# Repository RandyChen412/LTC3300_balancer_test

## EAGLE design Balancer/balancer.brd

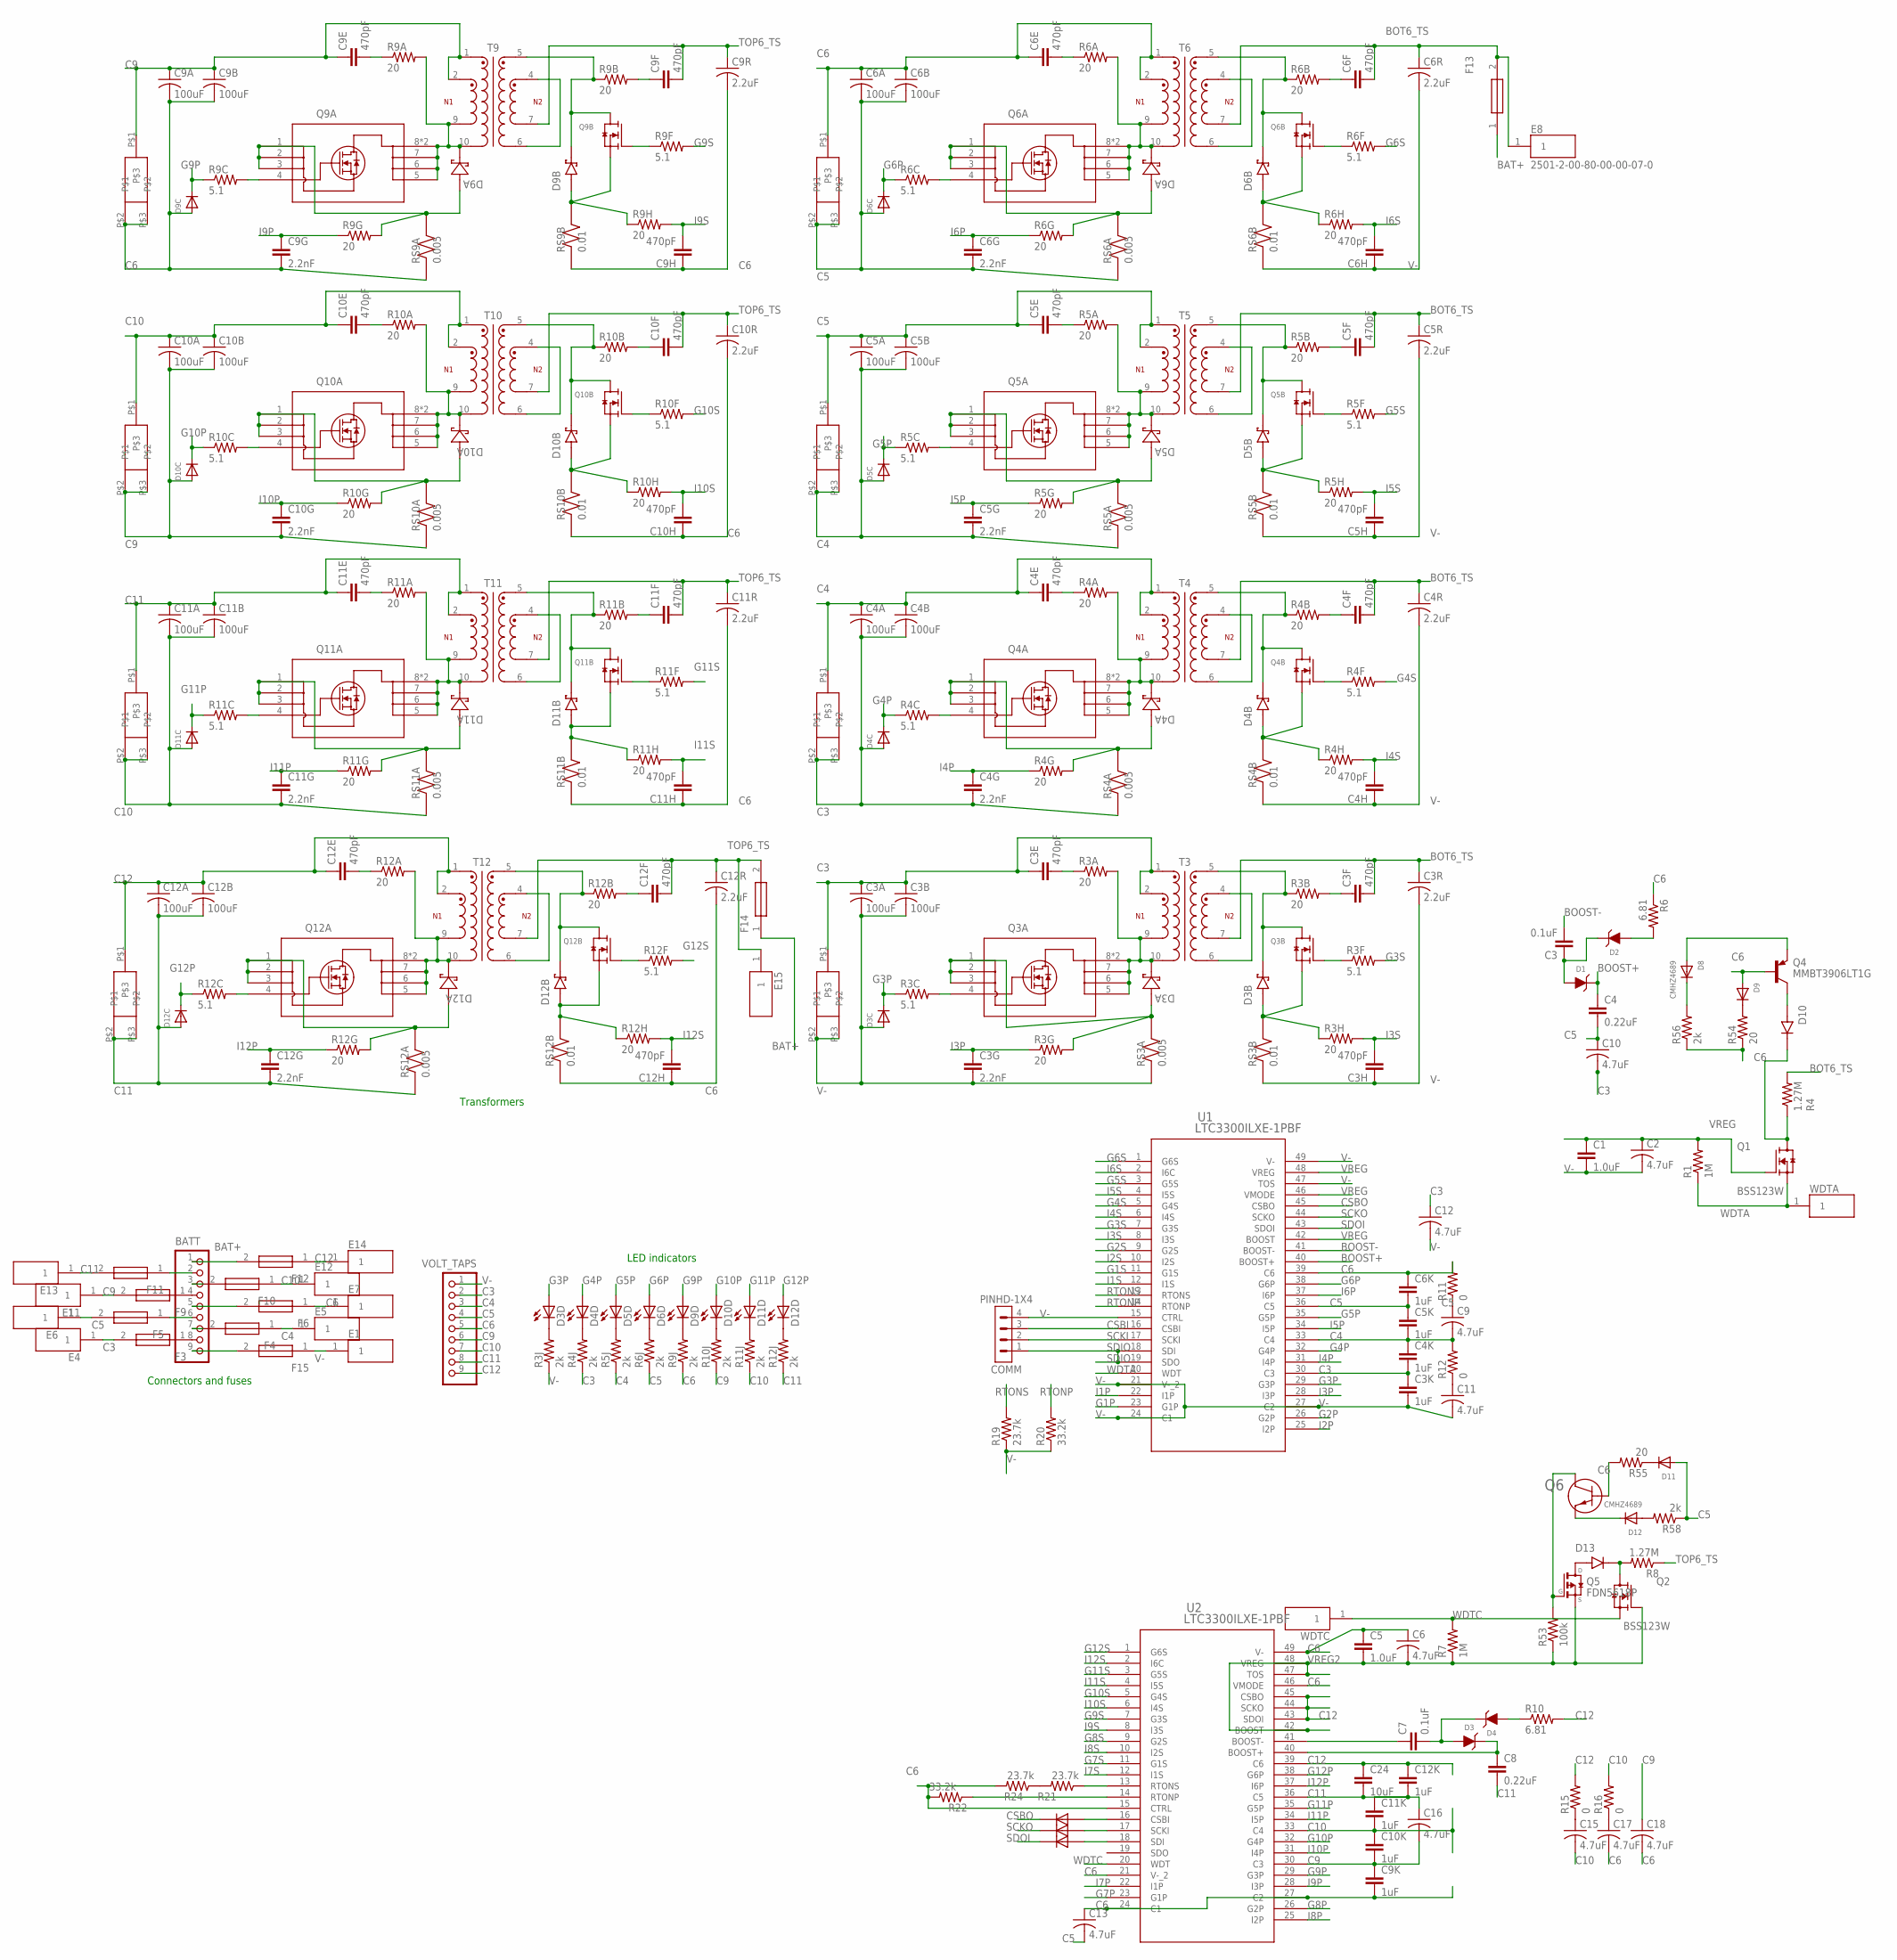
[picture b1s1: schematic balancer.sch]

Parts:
BATT: B9P-VH
C1, C5: 1.0uF; 0805
C2, C6, C9, C10, C11, C12, C13, C15, C16, C17, C18: 4.7uF; C1210
C3, C7: 0.1uF; 0805
C3A, C3B, C4A, C4B, C5A, C5B, C6A, C6B, C9A, C9B, C10A, C10B, C11A, C11B, C12A, C12B: 100uF; C1210
C3E, C3F, C3H, C4E, C4F, C4H, C5E, C5F, C5H, C6E, C6F, C6H, C9E, C9F, C9H, C10E, C10F, C10H, C11E, C11F, C11H, C12E, C12F, C12H: 470pF; 0805
C3G, C4G, C5G, C6G, C9G, C10G, C11G, C12G: 2.2nF; 0805
C3K, C4K, C5K, C6K, C9K, C10K, C11K, C12K: 1uF; 0805
C3R, C4R, C5R, C6R, C9R, C10R, C11R, C12R: 2.2uF; C1210
C4, C8: 0.22uF; 0805
C24: 10uF; 0805
COMM: PINHD-1X4; 1X04
D1, D2, D3, D4: WE-TVSP_DO-214AA_600W_UNI; WE-TVSP_DO-214AA_UNIDIRECTIONAL
D3A, D4A, D5A, D6A, D9A, D10A, D11A, D12A: DFLS260Q-7; SDO_POWERDI123_DIO
D3B, D4B, D5B, D6B, D9B, D10B, D11B, D12B: DFLS1100-7; DIO_DFLS1100-7
D3C, D4C, D5C, D6C, D9C, D10C, D11C, D12C: DIODESOD-523; SOD-523
D3D, D4D, D5D, D6D, D9D, D10D, D11D, D12D: LEDCHIPLED_0805; CHIPLED_0805
D3E, D4E, D5E, D6E, D9E, D10E, D11E, D12E: SBR10U200P5; POWERDI5
D5, D6, D7: RS07J-GS18; SODFL3718X108N
D8, D12: CMHZ4689; SOD-123
D9, D11: PDZ5.6B; SOD-323F
D10, D13: 1N4448HWT-7; SODFL1608X65N
E1, E4, E5, E6, E7, E8, E11, E12, E13, E14, E15: 2501-2-00-80-00-00-07-0; MILMAX_2501-2-00-80-00-00-07-0
F3, F4, F5, F6, F9, F10, F11, F12, F13, F14, F15: 01530008Z; 01530008
Q1, Q2: BSS123W; TRANS_BSS123W
Q3A, Q4A, Q5A, Q6A, Q9A, Q10A, Q11A, Q12A: SIR882DP-T1-GE3; POWERPAK_SO-8_SINGLE_VIS
Q3B, Q4B, Q5B, Q6B, Q9B, Q10B, Q11B, Q12B: SIS468DN-T1-GE3; VISHAY_SIS468DN-T1-GE3
Q4: MMBT3906LT1G; SOT95P240X111-3N
Q5: FDN5618P; SSOT-3
Q6: CMPT3904E_TR_PBFREE; CMPT-3904-NPN_CNS
R1, R7: 1M; 0805
R3A, R3B, R4A, R4B, R5A, R5B, R6A, R6B, R9A, R9B, R10A, R10B, R11A, R11B, R12A, R12B: 20; R1206
R3C, R3F, R4C, R4F, R5C, R5F, R6C, R6F, R9C, R9F, R10C, R10F, R11C, R11F, R12C, R12F: 5.1; 0805
R3G, R3H, R4G, R4H, R5G, R5H, R6G, R6H, R9G, R9H, R10G, R10H, R11G, R11H, R12G, R12H, R54, R55: 20; 0805
R3J, R4J, R5J, R6J, R9J, R10J, R11J, R12J: 2k; R0805
R4, R8: 1.27M; 0805
R6, R10: 6.81; 0805
R11, R12, R15, R16: 0; R2512
R19, R21, R24: 23.7k; 0805
R20, R22: 33.2k; 0805
R53: 100k; 0805
R56, R58: 2k; 0805
RS3A, RS4A, RS5A, RS6A, RS9A, RS10A, RS11A, RS12A: 0.005; RESC1632X60N
RS3B, RS4B, RS5B, RS6B, RS9B, RS10B, RS11B, RS12B: 0.01; RESC1632X60N
T3, T4, T5, T6, T9, T10, T11, T12: 750312504; WE-FLYLT_EP13_2381
U1, U2: LTC3300ILXE-1PBF; 05-08-1832_ADI
VOLT_TAPS: B9P-VH
WDTA: 2501-2-00-80-00-00-07-0; MILMAX_2501-2-00-80-00-00-07-0
WDTC: 2501-2-00-80-00-00-07-0; MILMAX_2501-2-00-80-00-00-07-0

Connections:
BAT+: BATT.1, F12.2, F13.1, F14.1
BOOST+: C4.1, D1.1 (C), U1.40 (BOOST+)
BOOST-: C3.2, U1.41 (BOOST-)
BOT6_TS: C3F.2, C3R.1, C4F.2, C4R.1, C5F.2, C5R.1, C6F.2, C6R.1, E8.1, F13.2, R4.2, T3.7, T4.7, T5.7, T6.7
C: D5.A, U2.16 (CSBI)
C3: C3A.1, C3B.1, C3E.1, C3K.1, C4A.2, C4B.2, C4G.2, C4K.2, C10.2, C12.1, D3E.P$1, D4C.A, D4E.P$2, D4E.P$3, E4.1, F3.2, R4J.1, RS4A.1, T3.1, T3.2, U1.30 (C3), VOLT_TAPS.2
C4: C4A.1, C4B.1, C4E.1, C4K.1, C5A.2, C5B.2, C5G.2, C5K.2, C9.2, D4E.P$1, D5C.A, D5E.P$2, D5E.P$3, E5.1, F4.1, R5J.1, R12.2, RS5A.1, T4.1, T4.2, U1.33 (C4), VOLT_TAPS.3
C5: C4.2, C5A.1, C5B.1, C5E.1, C5K.1, C6A.2, C6B.2, C6G.2, C6K.2, C10.1, C13.2, D5E.P$1, D6C.A, D6E.P$2, D6E.P$3, D11.A, E6.1, F5.2, R6J.1, R58.1, RS6A.1, T5.1, T5.2, U1.36 (C5), VOLT_TAPS.4
C6: C5.1, C6.1, C6A.1, C6B.1, C6E.1, C6K.1, C9A.2, C9B.2, C9G.2, C9H.1, C9K.2, C9R.2, C10H.1, C10R.2, C11H.1, C11R.2, C12H.1, C12R.2, C13.1, C17.2, C18.2, D6E.P$1, D9.A, D9C.A, D9E.P$2, D9E.P$3, E7.1, F6.1, Q4.1 (B), Q6.1, R6.1, R9J.1, R11.2, R22.2, R24.2, R54.1, R55.2, R56.1, RS9A.1, RS9B.1, RS10B.1, RS11B.1, RS12B.1, T6.1, T6.2, U1.39 (C6), U2.15 (CTRL), U2.21 (V-_2), U2.24 (C1), U2.27 (C2), U2.46 (VMODE), U2.49 (V-), VOLT_TAPS.5
C9: C9A.1, C9B.1, C9E.1, C9K.1, C10A.2, C10B.2, C10G.2, C10K.2, C16.2, C18.1, D9E.P$1, D10C.A, D10E.P$2, D10E.P$3, E11.1, F9.2, R10J.1, RS10A.1, T9.1, T9.2, U2.30 (C3), VOLT_TAPS.6
C10: C10A.1, C10B.1, C10E.1, C10K.1, C11A.2, C11B.2, C11G.2, C11K.2, C15.2, D10E.P$1, D11C.A, D11E.P$2, D11E.P$3, E12.1, F10.1, R11J.1, R16.2, RS11A.1, T10.1, T10.2, U2.33 (C4), VOLT_TAPS.7
C11: C8.2, C11A.1, C11B.1, C11E.1, C11K.1, C12A.2, C12B.2, C12G.2, C12K.2, C16.1, C24.2, D11E.P$1, D12C.A, D12E.P$2, D12E.P$3, E13.1, F11.2, R12J.1, RS12A.1, T11.1, T11.2, U2.36 (C5), VOLT_TAPS.8
C12: C12A.1, C12B.1, C12E.1, C12K.1, C24.1, D12E.P$1, E14.1, F12.1, R10.2, R15.2, T12.1, T12.2, U2.39 (C6), U2.43 (SDOI), U2.44 (SCKO), U2.45 (CSBO), VOLT_TAPS.9
CSBI: COMM.3, U1.16 (CSBI)
CSBO: D5.C, U1.45 (CSBO)
G1P: U1.23 (G1P)
G1S: U1.11 (G1S)
G2P: U1.26 (G2P)
G2S: U1.9 (G2S)
G3P: D3C.K (C), D3D.A, R3C.1, U1.29 (G3P)
G3S: R3F.2, U1.7 (G3S)
G4P: D4C.K (C), D4D.A, R4C.1, U1.32 (G4P)
G4S: R4F.2, U1.5 (G4S)
G5P: D5C.K (C), D5D.A, R5C.1, U1.35 (G5P)
G5S: R5F.2, U1.3 (G5S)
G6P: D6C.K (C), D6D.A, R6C.1, U1.38 (G6P)
G6S: R6F.2, U1.1 (G6S)
G7P: U2.23 (G1P)
G7S: U2.11 (G1S)
G8P: U2.26 (G2P)
G8S: U2.9 (G2S)
G9P: D9C.K (C), D9D.A, R9C.1, U2.29 (G3P)
G9S: R9F.2, U2.7 (G3S)
G10P: D10C.K (C), D10D.A, R10C.1, U2.32 (G4P)
G10S: R10F.2, U2.5 (G4S)
G11P: D11C.K (C), D11D.A, R11C.1, U2.35 (G5P)
G11S: R11F.2, U2.3 (G5S)
G12P: D12C.K (C), D12D.A, R12C.1, U2.38 (G6P)
G12S: R12F.2, U2.1 (G6S)
I1P: U1.22 (I1P)
I1S: U1.12 (I1S)
I2P: U1.25 (I2P)
I2S: U1.10 (I2S)
I3P: C3G.1, R3G.1, U1.28 (I3P)
I3S: C3H.2, R3H.2, U1.8 (I3S)
I4P: C4G.1, R4G.1, U1.31 (I4P)
I4S: C4H.2, R4H.2, U1.6 (I4S)
I5P: C5G.1, R5G.1, U1.34 (I5P)
I5S: C5H.2, R5H.2, U1.4 (I5S)
I6P: C6G.1, R6G.1, U1.37 (I6P)
I6S: C6H.2, R6H.2, U1.2 (I6C)
I7P: U2.22 (I1P)
I7S: U2.12 (I1S)
I8P: U2.25 (I2P)
I8S: U2.10 (I2S)
I9P: C9G.1, R9G.1, U2.28 (I3P)
I9S: C9H.2, R9H.2, U2.8 (I3S)
I10P: C10G.1, R10G.1, U2.31 (I4P)
I10S: C10H.2, R10H.2, U2.6 (I4S)
I11P: C11G.1, R11G.1, U2.34 (I5P)
I11S: C11H.2, R11H.2, U2.4 (I5S)
I12P: C12G.1, R12G.1, U2.37 (I6P)
I12S: C12H.2, R12H.2, U2.2 (I6C)
unnamed: C3.1, D1.2 (A), D2.1 (C)
unnamed: D2.2 (A), R6.2
unnamed: D10.A, Q4.3 (C)
unnamed: D8.C, R56.2
unnamed: D10.C (K), Q1.3 (D), R4.1
unnamed: D8.A, Q4.2 (E)
unnamed: D9.C, R54.2
unnamed: Q3A.4, R3C.2
unnamed: D3D.C, R3J.2
unnamed: T3.4, T3.6
unnamed: C3E.2, R3A.1
unnamed: D4D.C, R4J.2
unnamed: D5D.C, R5J.2
unnamed: BATT.2, F11.1
unnamed: D3A.2 (1), Q3A.5, Q3A.6, Q3A.7, Q3A.8, Q3A.9 (8), R3A.2, T3.9, T3.10
unnamed: D3A.1 (2), Q3A.1, Q3A.2, Q3A.3, R3G.2, RS3A.2
unnamed: C3F.1, R3B.2
unnamed: BATT.3, F10.2
unnamed: D3B.K, Q3B.5 (D), Q3B.6 (D), Q3B.7 (D), Q3B.8 (D), Q3B.9 (D), R3B.1, T3.5
unnamed: D3B.A, Q3B.1 (S), Q3B.2 (S), Q3B.3 (S), R3H.1, RS3B.2
unnamed: Q3B.4 (G), R3F.1
unnamed: BATT.4, F9.1
unnamed: BATT.5, F6.2
unnamed: Q4A.4, R4C.2
unnamed: BATT.6, F5.1
unnamed: BATT.7, F4.2
unnamed: C4E.2, R4A.1
unnamed: BATT.8, F3.1
unnamed: D4A.2 (1), Q4A.5, Q4A.6, Q4A.7, Q4A.8, Q4A.9 (8), R4A.2, T4.9, T4.10
unnamed: BATT.9, F15.2
unnamed: D4A.1 (2), Q4A.1, Q4A.2, Q4A.3, R4G.2, RS4A.2
unnamed: T4.4, T4.6
unnamed: C4F.1, R4B.2
unnamed: D6D.C, R6J.2
unnamed: D4B.K, Q4B.5 (D), Q4B.6 (D), Q4B.7 (D), Q4B.8 (D), Q4B.9 (D), R4B.1, T4.5
unnamed: D4B.A, Q4B.1 (S), Q4B.2 (S), Q4B.3 (S), R4H.1, RS4B.2
unnamed: D9D.C, R9J.2
unnamed: Q4B.4 (G), R4F.1
unnamed: D10D.C, R10J.2
unnamed: Q5A.4, R5C.2
unnamed: D11D.C, R11J.2
unnamed: D12D.C, R12J.2
unnamed: C5E.2, R5A.1
unnamed: R21.2, R24.1
unnamed: D5A.2 (1), Q5A.5, Q5A.6, Q5A.7, Q5A.8, Q5A.9 (8), R5A.2, T5.9, T5.10
unnamed: C7.2, D3.2 (A), D4.1 (C)
unnamed: D5A.1 (2), Q5A.1, Q5A.2, Q5A.3, R5G.2, RS5A.2
unnamed: T5.4, T5.6
unnamed: C5F.1, R5B.2
unnamed: D13.C (K), Q2.3 (D), R8.2
unnamed: D5B.K, Q5B.5 (D), Q5B.6 (D), Q5B.7 (D), Q5B.8 (D), Q5B.9 (D), R5B.1, T5.5
unnamed: D5B.A, Q5B.1 (S), Q5B.2 (S), Q5B.3 (S), R5H.1, RS5B.2
unnamed: D4.2 (A), R10.1
unnamed: Q5B.4 (G), R5F.1
unnamed: D13.A, Q5.3 (D)
unnamed: Q6A.4, R6C.2
unnamed: Q5.1 (G), Q6.3, R53.2
unnamed: D12.C, Q6.2
unnamed: C6E.2, R6A.1
unnamed: D12.A, R58.2
unnamed: D6A.2 (1), Q6A.5, Q6A.6, Q6A.7, Q6A.8, Q6A.9 (8), R6A.2, T6.9, T6.10
unnamed: D11.C, R55.1
unnamed: D6A.1 (2), Q6A.1, Q6A.2, Q6A.3, R6G.2, RS6A.2
unnamed: T6.4, T6.6
unnamed: C6F.1, R6B.2
unnamed: C9.1, R11.1
unnamed: D6B.K, Q6B.5 (D), Q6B.6 (D), Q6B.7 (D), Q6B.8 (D), Q6B.9 (D), R6B.1, T6.5
unnamed: D6B.A, Q6B.1 (S), Q6B.2 (S), Q6B.3 (S), R6H.1, RS6B.2
unnamed: C11.1, R12.1
unnamed: Q6B.4 (G), R6F.1
unnamed: Q9A.4, R9C.2
unnamed: R21.1, U2.13 (RTONS)
unnamed: R22.1, U2.14 (RTONP)
unnamed: C9E.2, R9A.1
unnamed: C15.1, R15.1
unnamed: D9A.2 (1), Q9A.5, Q9A.6, Q9A.7, Q9A.8, Q9A.9 (8), R9A.2, T9.9, T9.10
unnamed: D9A.1 (2), Q9A.1, Q9A.2, Q9A.3, R9G.2, RS9A.2
unnamed: T9.4, T9.6
unnamed: C9F.1, R9B.2
unnamed: D6.A, U2.17 (SCKI)
unnamed: D9B.K, Q9B.5 (D), Q9B.6 (D), Q9B.7 (D), Q9B.8 (D), Q9B.9 (D), R9B.1, T9.5
unnamed: D9B.A, Q9B.1 (S), Q9B.2 (S), Q9B.3 (S), R9H.1, RS9B.2
unnamed: D7.A, U2.18 (SDI)
unnamed: Q9B.4 (G), R9F.1
unnamed: Q10A.4, R10C.2
unnamed: C10E.2, R10A.1
unnamed: C17.1, R16.1
unnamed: D10A.2 (1), Q10A.5, Q10A.6, Q10A.7, Q10A.8, Q10A.9 (8), R10A.2, T10.9, T10.10
unnamed: D10A.1 (2), Q10A.1, Q10A.2, Q10A.3, R10G.2, RS10A.2
unnamed: T10.4, T10.6
unnamed: C10F.1, R10B.2
unnamed: D10B.K, Q10B.5 (D), Q10B.6 (D), Q10B.7 (D), Q10B.8 (D), Q10B.9 (D), R10B.1, T10.5
unnamed: D10B.A, Q10B.1 (S), Q10B.2 (S), Q10B.3 (S), R10H.1, RS10B.2
unnamed: Q10B.4 (G), R10F.1
unnamed: Q11A.4, R11C.2
unnamed: C11E.2, R11A.1
unnamed: D11A.2 (1), Q11A.5, Q11A.6, Q11A.7, Q11A.8, Q11A.9 (8), R11A.2, T11.9, T11.10
unnamed: D11A.1 (2), Q11A.1, Q11A.2, Q11A.3, R11G.2, RS11A.2
unnamed: T11.4, T11.6
unnamed: C11F.1, R11B.2
unnamed: D11B.K, Q11B.5 (D), Q11B.6 (D), Q11B.7 (D), Q11B.8 (D), Q11B.9 (D), R11B.1, T11.5
unnamed: D11B.A, Q11B.1 (S), Q11B.2 (S), Q11B.3 (S), R11H.1, RS11B.2
unnamed: Q11B.4 (G), R11F.1
unnamed: Q12A.4, R12C.2
unnamed: C12E.2, R12A.1
unnamed: D12A.2 (1), Q12A.5, Q12A.6, Q12A.7, Q12A.8, Q12A.9 (8), R12A.2, T12.9, T12.10
unnamed: D12A.1 (2), Q12A.1, Q12A.2, Q12A.3, R12G.2, RS12A.2
unnamed: T12.4, T12.6
unnamed: C12F.1, R12B.2
unnamed: D12B.K, Q12B.5 (D), Q12B.6 (D), Q12B.7 (D), Q12B.8 (D), Q12B.9 (D), R12B.1, T12.5
unnamed: D12B.A, Q12B.1 (S), Q12B.2 (S), Q12B.3 (S), R12H.1, RS12B.2
unnamed: Q12B.4 (G), R12F.1
unnamed: C8.1, D3.1 (C), U2.40 (BOOST+)
unnamed: C7.1, U2.41 (BOOST-)
RTONP: R20.2, U1.14 (RTONP)
RTONS: R19.2, U1.13 (RTONS)
SCKI: COMM.2, U1.17 (SCKI)
SCKO: D6.C, U1.44 (SCKO)
SDIO: COMM.1, U1.18 (SDI), U1.19 (SDO)
SDOI: D7.C, U1.43 (SDOI)
TOP6_TS: C9F.2, C9R.1, C10F.2, C10R.1, C11F.2, C11R.1, C12F.2, C12R.1, E15.1, F14.2, R8.1, T9.7, T10.7, T11.7, T12.7
V-: C1.2, C2.2, C3A.2, C3B.2, C3G.2, C3H.1, C3K.2, C3R.2, C4H.1, C4R.2, C5H.1, C5R.2, C6H.1, C6R.2, C11.2, C12.2, COMM.4, D3C.A, D3E.P$2, D3E.P$3, E1.1, F15.1, R3J.1, R19.1, R20.1, RS3A.1, RS3B.1, RS4B.1, RS5B.1, RS6B.1, U1.15 (CTRL), U1.21 (V-_2), U1.24 (C1), U1.27 (C2), U1.47 (TOS), U1.49 (V-), VOLT_TAPS.1
VREG: C1.1, C2.1, Q1.1 (G), R1.2, U1.42 (BOOST), U1.46 (VMODE), U1.48 (VREG)
VREG2: C5.2, C6.2, Q2.1 (G), Q5.2 (S), R7.1, R53.1, U2.42 (BOOST), U2.47 (TOS), U2.48 (VREG)
WDTA: Q1.2 (S), R1.1, U1.20 (WDT), WDTA.1
WDTC: Q2.2 (S), R7.2, U2.20 (WDT), WDTC.1

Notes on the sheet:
Connectors and fuses
Transformers
LED indicators

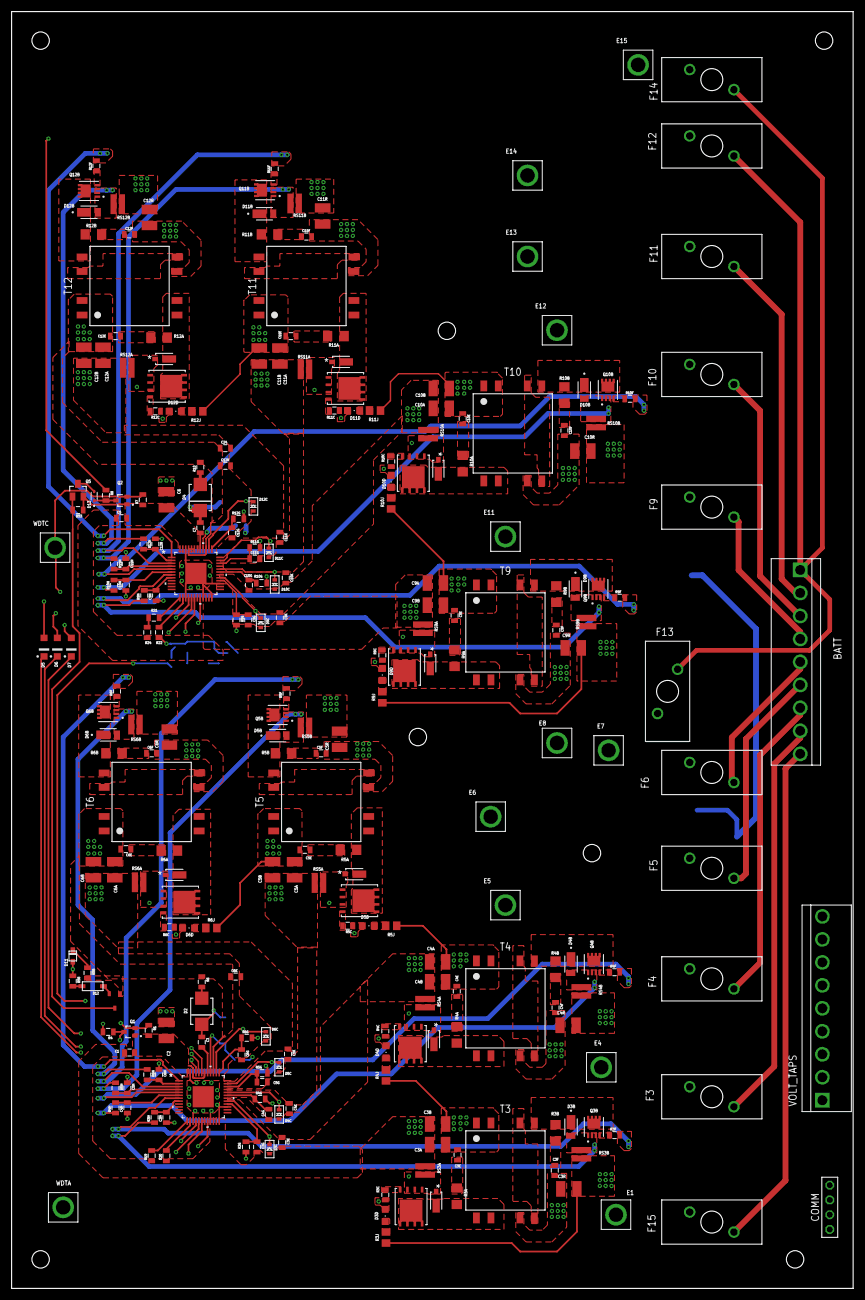
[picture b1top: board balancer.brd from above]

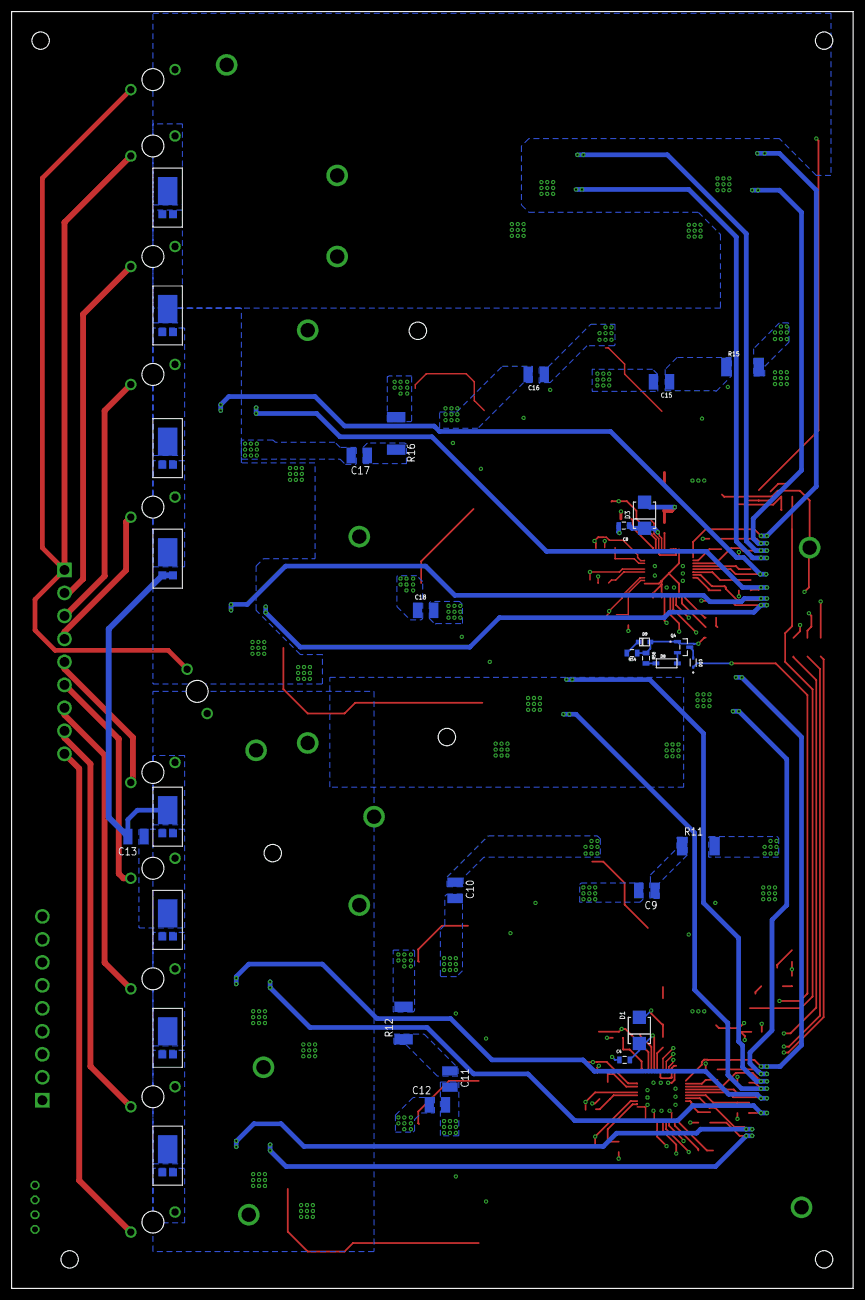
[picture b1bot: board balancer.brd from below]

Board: 4 copper layers, 145.0 x 220.0 mm, 285 parts (31 on the bottom side), 173 nets.

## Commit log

2026-02-12 created documents
2026-02-12 deleted pullups for CSBI
2026-02-12 deleted C14 and moved C12 to correct position
2026-02-12 removed one lowpass resistor, did schematic check
2026-02-14 created .brd file
2026-02-15 Placed front components
2026-02-15 update1
2026-02-15 Resolved errors and approved warnings
2026-02-15 changed layout
2026-02-16 removed R5 & placed all component on PCB
2026-02-17 drew PCB
2026-02-18 made more changes on board
2026-02-18 made more connections on pcb
2026-02-18 made traces on L1 of PCB
2026-02-18 Did the top 2 copper pours in layer 2, unsure about "inner" upper left corner geometry
2026-02-18 merged C8 and C6
2026-02-18 made more connections on L1 PCB
2026-02-19 Finished L2 and L3 Copper Pours
2026-02-19 Placed more components on L1
2026-02-19 Revert "Placed more components on L1"
2026-02-19 mystery update
2026-02-19 done most of L1 wiring
2026-02-19 done majority of L1 wiring
2026-02-19 modified position of E8 and E15
2026-02-20 L1 mostly done, L2 done
2026-02-20 Finished L3 wiring
2026-02-20 finished L3 and get half of L4 done
2026-02-20 Finished PCB drawing
2026-02-20 done final check, generated Gerber file
2026-02-20 uploaded zip version of GBR
2026-02-21 BOM for JLCPCB, use xlsx version
2026-02-21 CPL for JLCPCB, b for back and t for top layer
2026-02-21 updated BOM and CPL
2026-02-23 fixed wrong library on D3A-D12A
2026-02-23 replaced RSnA and RSnB to correct parts
2026-02-23 placed RSnA and RSnB
2026-02-24 created new pick list and GBR file
2026-02-25 removed older version of Gerber and BOM, check new BOM in google drive
2026-02-25 merged all lbr to one single file
2026-03-16 random updates

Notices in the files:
parts and their libraries:
COPYRIGHT: Copyright (C) 2026 Ultra Librarian. All rights reserved.
